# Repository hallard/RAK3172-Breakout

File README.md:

# RAK3172 breakout board

Based on [RAK3172](https://docs.rakwireless.com/Product-Categories/WisDuo/RAK3172-Module/Overview/) from RAK Wireless.

I'm using mainly to flash custom firmware in it, and not using AT default firmware.

##Changes log

**V1.1**

- Fixed Boot0 wiring to 3V3 instead of ground
- Fixed BOM on schematics 

**V1.0**

- RAK3172 Module
- No USB/Serial, SMD FTDI 6 pins connector (**use 3.3V FTDI One, not 5V**)
- Exposed JTAG pins needed to flash module (PA13-SWDIO / PA14-SWCLK / RESET)
- Red Led on PB5
- Green Led on PB10
- Optional 2 Tactile Switch (boot and reset)
- I2C 4 pins location for "classic" sensors

## Detailed Description

No specific documentation for now, it's just a kind of wiring helper as schematic

## Schematic

## Boards 

You can order the board on [oshpark](https://oshpark.com). 

- [V1.1](https://oshpark.com/shared_projects/s3n0gTxi) 
- [V1.0](https://oshpark.com/shared_projects/Ss2INNiR) 

It's a pitty after several discuss with OSHPark that I can't have any rewards for each people ordering my boards, this would allow me to order free PCB for shared projects and create new ones. For information my shared boards generated a total of **$285 162.00** orders at PCBs.io in 4 years, not bad at all :-)

Hoping one day OSHparks will thanks me giving them this market. 

### Assembled boards

**Top & bottom side**

TBD

## Bill Of Material

Nothing fancy, all components are 0805 and/or PTH and can be ordered almost anywhere (digikey, mouser, radiospare, ...). 
use only what you need dependings on what you want to do. 

Check [BOM](https://github.com/hallard/RAK3172-Breakout/blob/main/RAK3172-Breakout-BOM.xlsx) File.

PS : 100uF 0805 capacitors C4,C5,C6 and C7 are for use with coin cell battery, no need to put them if not powering from coin. Also take care of contact is using cell coin

### Test Board out of factory stock 

When the boards are from factory, default AT firmware is flashed and thus we have the possibility to test the board before flashing custom firmware and maily also get defaults keys from device.

To do so, connect a 3V3 FTDI Type USB/Serial to access Serial Console 

> :warning: **Do not use 5V configured FTDI** 

I personnaly use these one for [Sparkun](https://www.sparkfun.com/products/14050) but you can find clones anywhere on the Web.

Once done open Serial terminal (the one from FTDI Serial Port) configured as `9600` BPS `8N1`, no flow control, echo typed characters and set to CR+LF for enter key, press reset button and you should be able to see banner

```
LoRa (R) is a registered trademark or service mark of Semtech Corporation or its affiliates. LoRaWAN (R) is a licensed mark.

______  ___   _   __  _    _ _          _               
| ___ \/ _ \ | | / / | |  | (_)        | |              
| |_/ / /_\ \| |/ /  | |  | |_ _ __ ___| | ___  ___ ___ 
|    /|  _  ||    \  | |/\| | | '__/ _ \ |/ _ \/ __/ __|
| |\ \| | | || |\  \ \  /\  / | | |  __/ |  __/\__ \__ \
\_| \_\_| |_/\_| \_/  \/  \/|_|_|  \___|_|\___||___/___/
========================================================
RAK3172-H Version:v1.0.2 May 26 2021
Current Work Mode: LoRaWAN.
```

Then type `AT` command to see if the RAK board answer, in this example the board answered `OK` which is correct
```
AT 
OK
```

Now get the device version
```
AT+VER=? 
V1.0.2
OK
```

Now get the device keys information 
```
AT+DEVEUI=? 
ac1f09fffe0527f5
OK
AT+APPEUI=? 
ac1f09fff8683172
OK
AT+APPKEY=? 
ac1f09fffe0527f5ac1f09fff8683172
OK
```

I'm using [TTN](https://www.thethingsnetwork.org/) for testing so please follow excellent RAK guide on how to provision your device onto TTN [here](https://docs.rakwireless.com/Product-Categories/WisDuo/RAK3172-Module/Quickstart/#connecting-to-the-things-network-ttn)

In our case we will use the AppKey generated from TTN when provisionning device, just provision your device onto TTN, get the key and put into the device as follow with command `AT+APPKEY` in our case AppKey is `B3D2F9587DED7B03AD9F1809564192E0`
```
AT+APPKEY=B3D2F9587DED7B03AD9F1809564192E0 
OK
```
Check it's ok
```
AT+APPKEY=?                                
b3d2f9587ded7b03ad9f1809564192e0
OK
```

Set LoRaWAN Mode + OTAA + Class A + Frequency Plan EU868 (Band 4) + ADR
```
AT+NWM=1 
OK

AT+NJM=1 
OK

AT+CLASS=A 
OK

AT+BAND=4 
OK

AT+ADR=1 
OK
```

Now time to join (be sure device is provisioned on TTN and you have a TTN gateway around)
```
AT+JOIN=1:0:10:8 
OK
```

some seconds later you should have confirmation
```
+EVT:JOINED
```

Now send ASCII "1234" confirmed message
```
AT+SEND=2:31323334 
OK
+EVT:SEND CONFIRMED OK
```

And here we go, all is working fine, now time to have some fun with custom firmware

### Compile and flash Firmware

You can flash the board with excellent [mbed-os](https://os.mbed.com/mbed-os/) framework. 
Easy way is to use [mbed studio IDE](https://os.mbed.com/studio/). 
We added this board into [stm32customtargets](https://github.com/ARMmbed/stm32customtargets), don't hesitate to read the [readme](https://github.com/ARMmbed/stm32customtargets/blob/master/README.md). 
Finally the main firmware [mbed-os-example-lorawan](https://github.com/ARMmbed/mbed-os-example-lorawan) program.

Once IDE installed: 

- use `file` / `import program` and them import the example with URL `https://github.com/ARMmbed/mbed-os-example-lorawan`
- right click in the project name and select `Add Library` and enter `https://github.com/ARMmbed/stm32customtargets`
- open the file `custom_targets.json` from folder `stm32customtargets` and copy whole contents
- paste copied contents in the main root folder file `custom_targets.json` (yes replace the whole file) 
- open the file `mbed_app.json` and change parameters on the section `target_overrides`
    - LoRaWAN parameters such as frequency plan, OTAA, Duty Cycle, ...
    - replace keys with the ones you got from above step `lora.device-eui`, `lora.application-eui` and `lora.application-key`
- add the following section near the end of the file `mbed_app.json`.

```json
        "RAK3172_BREAKOUT": {
            "stm32wl-lora-driver.rf_switch_config": 2,
            "stm32wl-lora-driver.crystal_select": 0,
            "stm32wl-lora-driver.debug_rx": "LED1",
            "stm32wl-lora-driver.debug_tx": "LED2",
            "stm32wl-lora-driver.debug_invert": 1
        }
```

Then on IDE select target "RAK3172_BREAKOUT", build and flash with your favorite programmer (I'm using STLink) with GND/SWDIO/SWDCLK/RESET connected. 

### Build and Flash

From IDE you can build the example. If you plug your STLink while project opened, mbed ide will ask you if you want to set it up for this project/target, once approved you can compile, flash and even debug from mbed ide (need some tools installed, [read](https://os.mbed.com/docs/mbed-studio/current/monitor-debug/debugging-with-mbed-studio.html), very nice.

You can also see logs with the FTDI adapter and any Serial terminal set to 115200 bauds 8 bits no parity 1 stop bit (8N1)

```
Mbed LoRaWANStack initialized 
 CONFIRMED message retries : 3 
 Adaptive data  rate (ADR) - Enabled 
 Connection - In Progress ...
 Connection - Successful 
 Dummy Sensor Value = 3 
 23 bytes scheduled for transmission 
 Message Sent to Network Server 
 Dummy Sensor Value = 5 
 23 bytes scheduled for transmission 
 Message Sent to Network Server 
 Dummy Sensor Value = 7 
 23 bytes scheduled for transmission 
```

Green LED will be on when on receive mode and Red when sending data.

## License

This work is licensed under a [Creative Commons Attribution-NonCommercial-ShareAlike 4.0 International License](https://creativecommons.org/licenses/by-nc-sa/4.0/)    
If you want to do commercial stuff with this project, please contact [CH2i company](https://www.ch2i.eu/en#support) so we can organize an simple agreement.

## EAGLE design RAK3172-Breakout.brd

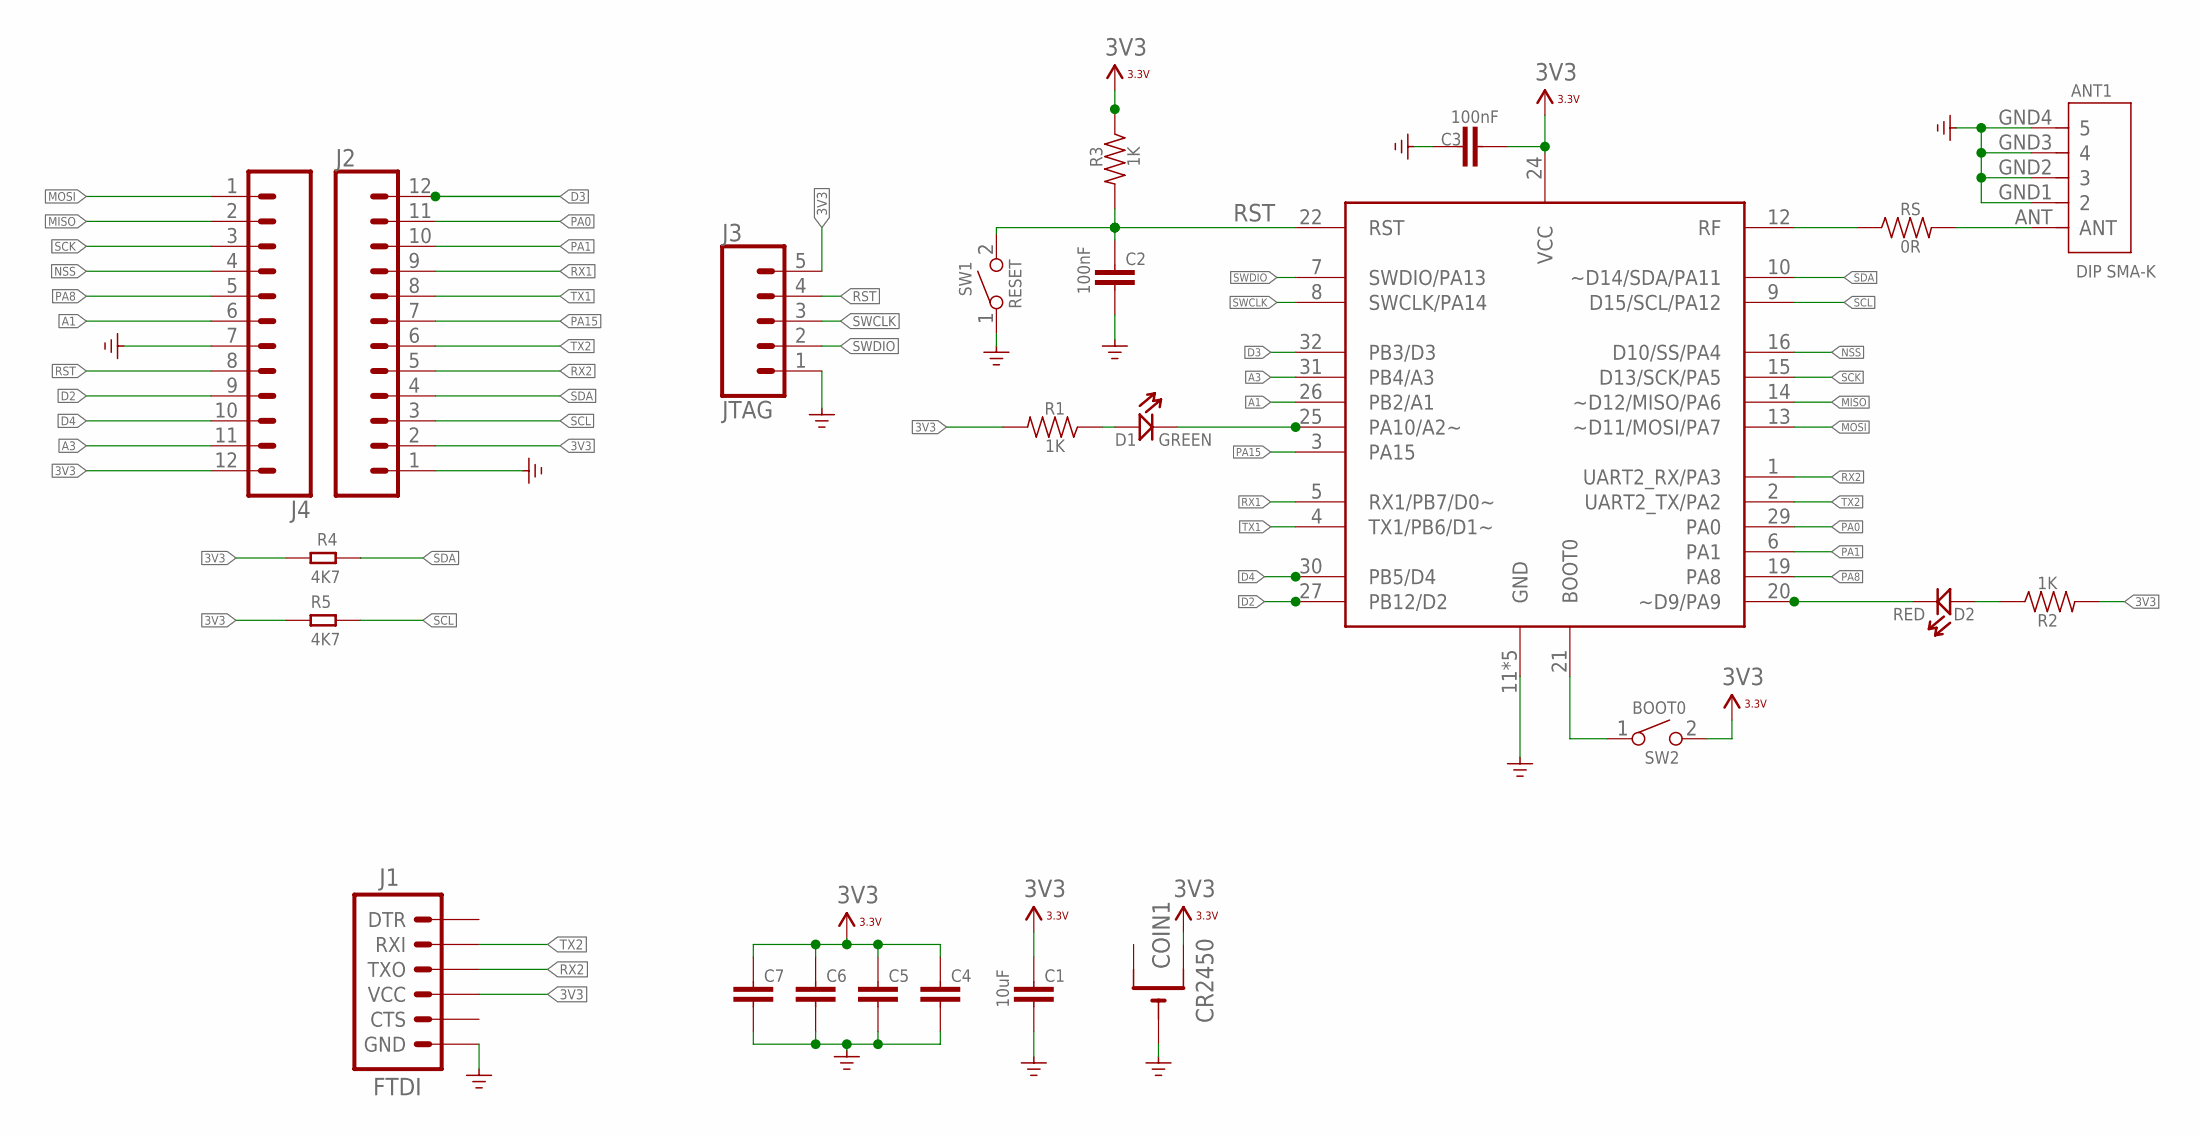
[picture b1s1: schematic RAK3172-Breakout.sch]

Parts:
ANT1: DIP SMA-K; SMA5P-SMD-5.1-6.5X6.5X16.5MM
C1: 10uF; 0805-CAP
C2, C3: 100nF; 0805-CAP
C4, C5, C6, C7: 100uF; 0805-CAP
COIN1: CR2450; CR2450-SMD
D1: GREEN; LED-0805
D2: RED; LED-0805
J1: FTDI; 1X06-SMD_RA_MALE
J2, J4: CONN_12NO_SILK; 1X12_NO_SILK
J3: JTAG; 1X05_LOCK
R1, R2, R3: 1K; 0805-RES
R4, R5: 4K7; R0805
RS: 0R; 0603-MATCHNET
SW1: RESET; SW2-2.6-3.0X2.5X1.2+0.4MM
SW2: BOOT0; SW2-2.6-3.0X2.5X1.2+0.4MM
U$3: RAK3172HF; RAK3172

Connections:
3V3: C1.2, C3.2, C4.2, C5.2, C6.2, C7.2, COIN1.+$2 (+1), J1.4 (VCC), J2.2, J3.5, J4.12, R1.2, R2.2, R3.1, R4.1, R5.1, SW2.2, U$3.24 (VCC)
A1: J4.6, U$3.26 (PB2/A1)
A3: J4.11, U$3.31 (PB4/A3)
D2: J4.9, U$3.27 (PB12/D2)
D3: J2.12, U$3.32 (PB3/D3)
D4: J4.10, U$3.30 (PB5/D4)
GND: ANT1.GND1 (2), ANT1.GND2 (3), ANT1.GND3 (4), ANT1.GND4 (5), C1.1, C2.1, C3.1, C4.1, C5.1, C6.1, C7.1, COIN1.-, J1.6 (GND), J2.1, J3.1, J4.7, SW1.1, U$3.11 (GND), U$3.17 (GND), U$3.18 (GND), U$3.23 (GND), U$3.28 (GND)
GREEN: D1.-, U$3.25 (PA10/A2~)
MISO: J4.2, U$3.14 (~D12/MISO/PA6)
MOSI: J4.1, U$3.13 (~D11/MOSI/PA7)
unnamed: D1.+, R1.1
unnamed: SW2.1, U$3.21 (BOOT0)
unnamed: D2.+, R2.1
unnamed: ANT1.ANT, RS.2
NSS: J4.4, U$3.16 (D10/SS/PA4)
PA0: J2.11, U$3.29 (PA0)
PA1: J2.10, U$3.6 (PA1)
PA8: J4.5, U$3.19 (PA8)
PA15: J2.7, U$3.3 (PA15)
RED: D2.-, U$3.20 (~D9/PA9)
RF: RS.1, U$3.12 (RF)
RST: C2.2, J3.4, J4.8, R3.2, SW1.2, U$3.22 (RST)
RX1: J2.9, U$3.5 (RX1/PB7/D0~)
RX2: J1.3 (TXO), J2.5, U$3.1 (UART2_RX/PA3)
SCK: J4.3, U$3.15 (D13/SCK/PA5)
SCL: J2.3, R5.2, U$3.9 (D15/SCL/PA12)
SDA: J2.4, R4.2, U$3.10 (~D14/SDA/PA11)
SWCLK: J3.3, U$3.8 (SWCLK/PA14)
SWDIO: J3.2, U$3.7 (SWDIO/PA13)
TX1: J2.8, U$3.4 (TX1/PB6/D1~)
TX2: J1.2 (RXI), J2.6, U$3.2 (UART2_TX/PA2)

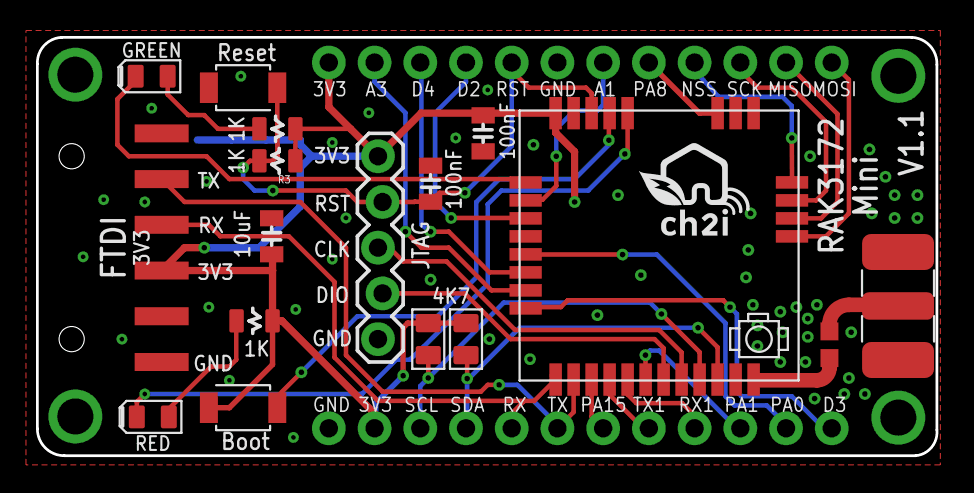
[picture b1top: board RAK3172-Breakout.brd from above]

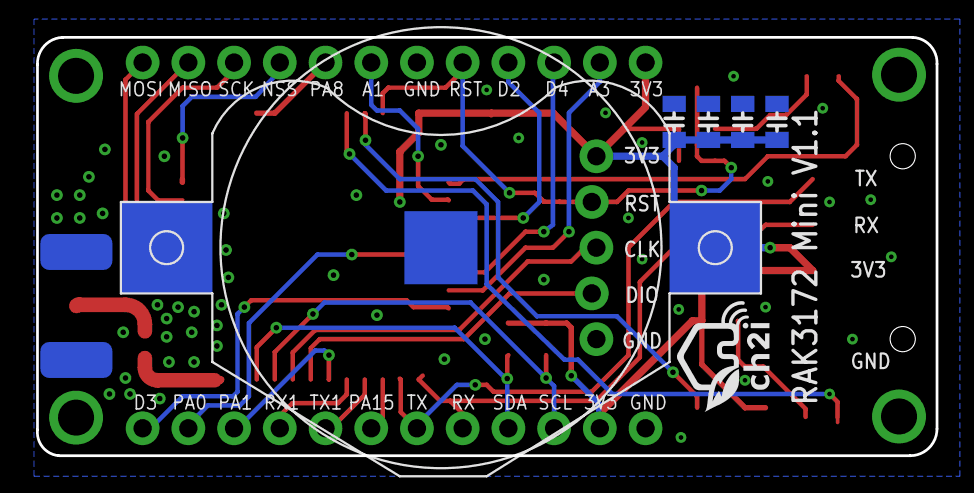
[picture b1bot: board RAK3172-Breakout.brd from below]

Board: 2 copper layers, 50.0 x 23.2 mm, 26 parts (6 on the bottom side), 31 nets.

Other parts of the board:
U$1, U$2: LOGO_C2I_015

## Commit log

2021-07-05 Renamed
2021-07-05 Update README.md
    added license
2021-07-20 assembled picture
2021-08-18 Add compile an build FW
2021-08-18 added factory testing
2023-05-26 Bump to V1.1
2023-05-26 fixed revision to V1.1
2026-04-29 Switch to CC BY-NC-SA 4.0 license, add LICENSE file

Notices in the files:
parts and their libraries:
SparkFun-Connectors: Licensing: Creative Commons ShareAlike 4.0 International - https://creativecommons.org/licenses/by-sa/4.0
PatternAgents-Beautify: License : http://creativecommons.org/licenses/by-sa/3.0
(Creative Commons 3.0)
